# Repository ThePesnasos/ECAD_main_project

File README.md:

# ECAD_main_project
# Печатная плата для аналогового и цифровго трактов ЭЭГ
Для сборки аппарата ЭЭГ необходимо произвести 8 плат аналоговго тракта и 1 плату цифрового.
Плата цифрового тракта объединяется с 8 платами аналогового тракта

# TODO
1. В результате разводки платы выявлено отсутвие пинов для подключения питания 5В и 3,3 В.
Необходимо доработать схемотехническую часть, использовать разъёмы с большим числом пинов.

2. Предусмотреть отверстия под крепления печатных плат в корпусе устройства.

3. Рассмотреть возможность создания третьей "материнской", чтобы избежать использования разъемов с проводами внутри прибора.

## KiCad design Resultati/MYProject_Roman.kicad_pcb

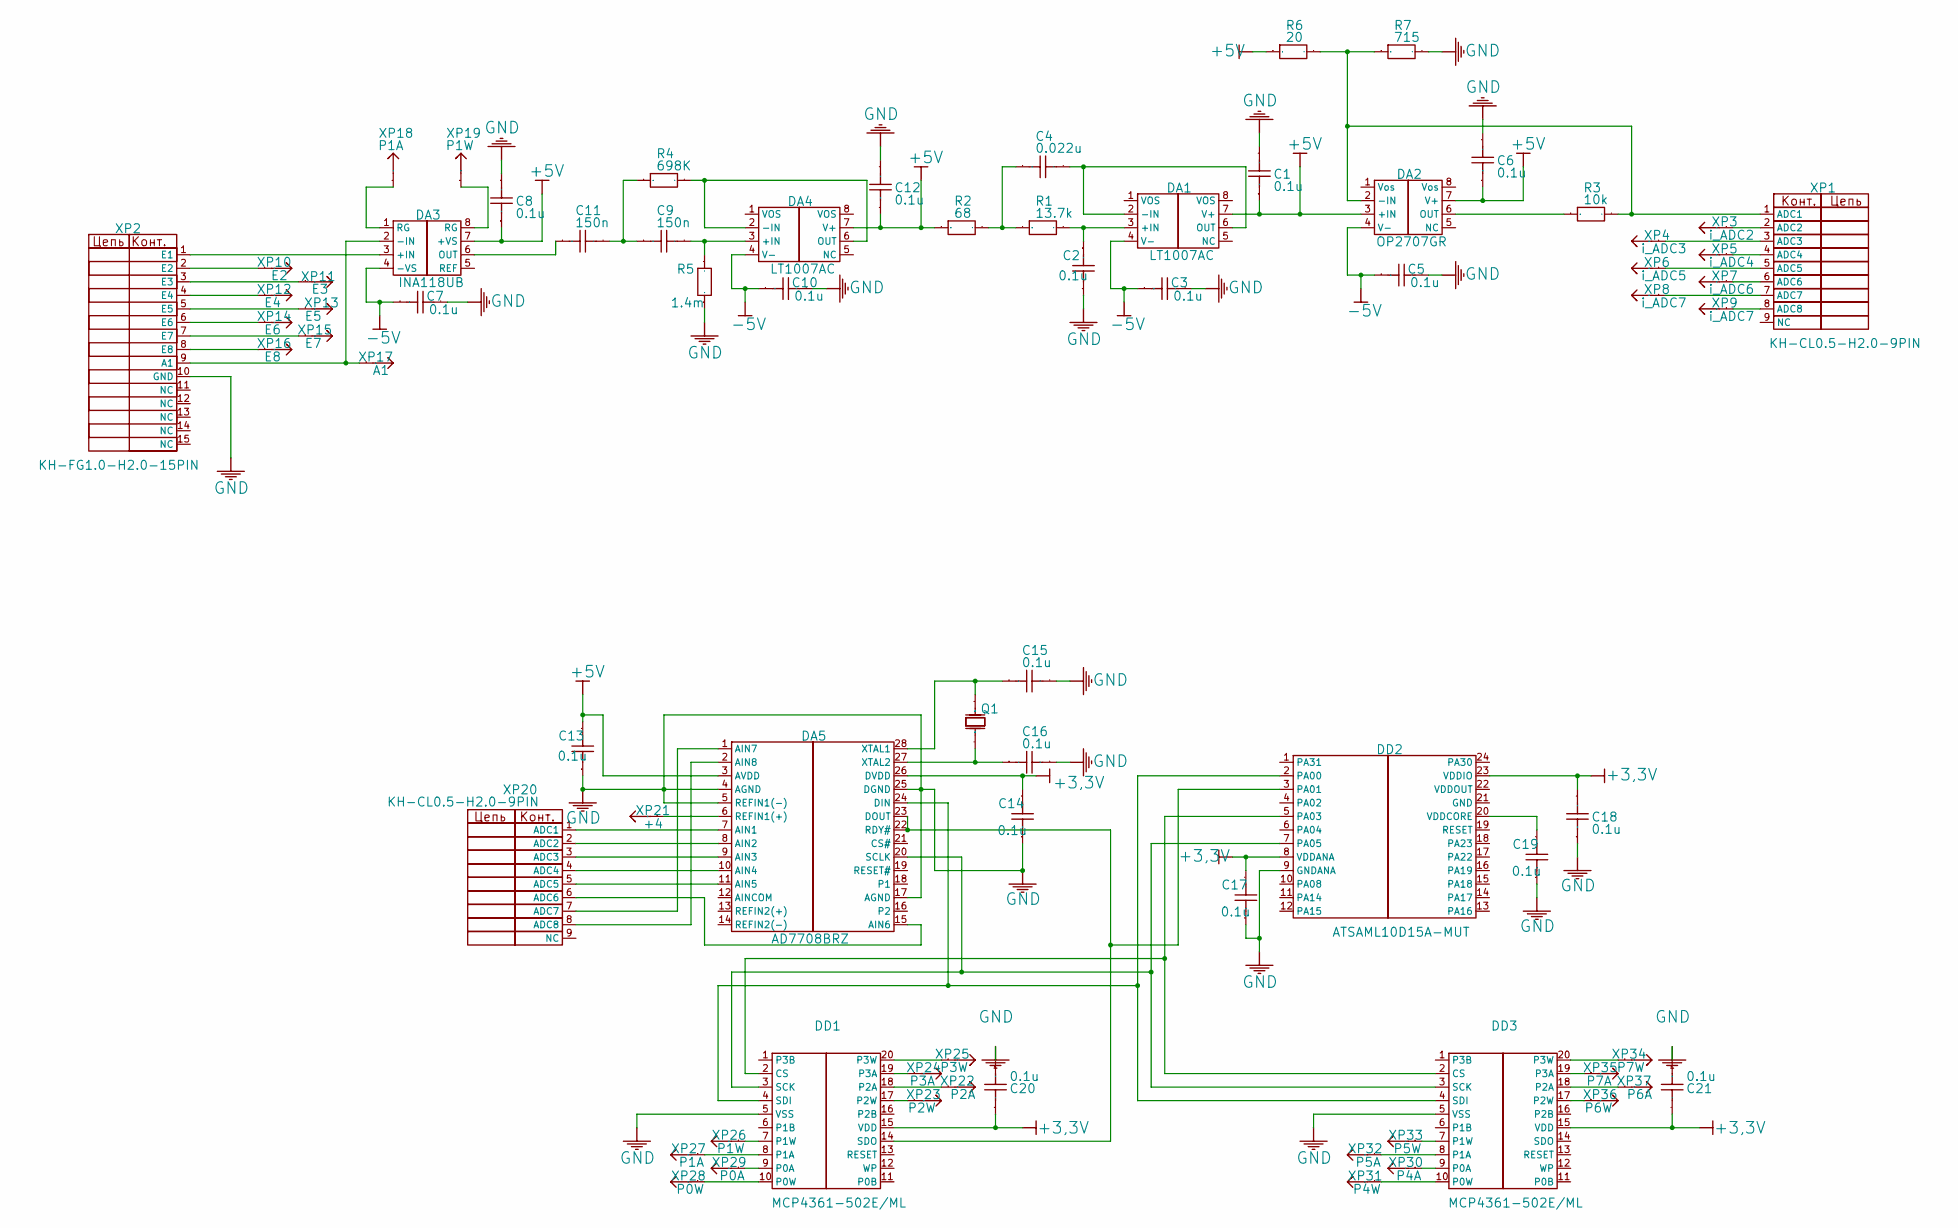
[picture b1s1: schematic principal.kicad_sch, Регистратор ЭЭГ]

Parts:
C1, C2, C3, C5, C6, C7, C8, C10, C12, C13, C14, C15, C16, C17, C18, C19, C20, C21: 0.1u
C4: 0.022u
C9, C11: 150n
DA1, DA4: LT1007AC; Manufacturer Part LT1007ACN8#PBF
DA2: OP2707GR; Manufacturer Part NJMOP277GR-TE1
DA3: INA118UB; Manufacturer Part INA118UB
DA5: AD7708BRZ; Manufacturer Part AD7708BRZ
DD1, DD3: MCP4361-502E/ML; Manufacturer Part MCP4361-502E/ML
DD2: ATSAML10D15A-MUT; Manufacturer Part ATSAML10D15A-MUT
Q1: HC-49SMD-XTAL_MD; Manufacturer Part HC-49SMD-XTAL_MD
R1: 13.7k
R2: 68
R3: 10k
R4: 698K
R5: 1.4m
R6: 20
R7: 715
XP1, XP20: KH-CL0.5-H2.0-9PIN; Manufacturer Part KH-CL0.5-H2.0-9PIN
XP2: KH-FG1.0-H2.0-15PIN; Manufacturer Part KH-FG1.0-H2.0-15PIN
XP3: i_ADC2
XP4: i_ADC3
XP5: i_ADC4
XP6: i_ADC5
XP7: i_ADC6
XP8, XP9: i_ADC7
XP10: E2
XP11: E3
XP12: E4
XP13: E5
XP14: E6
XP15: E7
XP16: E8
XP17: A1
XP18, XP27: P1A
XP19, XP26: P1W
XP21: +4
XP22: P2A
XP23: P2W
XP24: P3A
XP25: P3W
XP28: P0W
XP29: P0A
XP30: P4A
XP31: P4W
XP32: P5A
XP33: P5W
XP34: P7W
XP35: P7A
XP36: P6W
XP37: P6A

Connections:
+3,3V: C14.2, C17.2, C18.2, C20.2, C21.2, DA5.26 (DVDD), DD1.15 (VDD), DD2.8 (VDDANA), DD2.23 (VDDIO), DD3.15 (VDD)
-5V: C3.1, C5.1, C7.1, C10.1, DA1.4 (V-), DA2.4 (V−), DA3.4 (-VS), DA4.4 (V-)
DA1_1: DA1.1 (VOS)
DA1_2: C4.2, DA1.2 (-IN), DA1.6 (OUT)
DA1_3: C2.1, DA1.3 (+IN), R1.2
DA1_5: DA1.5 (NC)
DA1_8: DA1.8 (VOS)
DA2_1: DA2.1 (Vos)
DA2_2: DA2.2 (−IN), R3.2, R6.2, R7.1, XP1.1 (ADC1)
DA2_5: DA2.5 (NC)
DA2_6: DA2.6 (OUT), R3.1
DA2_8: DA2.8 (Vos)
DA3_1: DA3.1 (RG), XP18.1
DA3_5: DA3.5 (REF)
DA3_8: DA3.8 (RG), XP19.1
DA4_1: DA4.1 (VOS)
DA4_2: DA4.2 (-IN), DA4.6 (OUT), R4.2
DA4_3: C9.2, DA4.3 (+IN), R5.2
DA4_5: DA4.5 (NC)
DA4_8: DA4.8 (VOS)
DA5_6: DA5.6 (REFIN1(+)), XP21.1
DA5_12: DA5.12 (AINCOM)
DA5_13: DA5.13 (REFIN2(+))
DA5_14: DA5.14 (REFIN2(-))
DA5_16: DA5.16 (P2)
DA5_18: DA5.18 (P1)
DA5_19: DA5.19 (RESET#)
DA5_20: DA5.20 (SCLK), DD1.3 (SCK), DD2.7 (PA05), DD3.3 (SCK)
DA5_21: DA5.21 (CS#)
DA5_24: DA5.24 (DIN), DD1.4 (SDI), DD2.2 (PA00), DD3.4 (SDI)
DA5_27: C16.1, DA5.27 (XTAL2), Q1.2 (OSC2)
DA5_28: C15.1, DA5.28 (XTAL1), Q1.1 (OSC1)
DD1_1: DD1.1 (P3B)
DD1_6: DD1.6 (P1B)
DD1_7: DD1.7 (P1W), XP26.1
DD1_8: DD1.8 (P1A), XP27.1
DD1_9: DD1.9 (P0A), XP29.1
DD1_10: DD1.10 (P0W), XP28.1
DD1_11: DD1.11 (P0B)
DD1_12: DD1.12 (WP)
DD1_13: DD1.13 (RESET)
DD1_16: DD1.16 (P2B)
DD1_17: DD1.17 (P2W), XP23.1
DD1_18: DD1.18 (P2A), XP22.1
DD1_19: DD1.19 (P3A), XP24.1
DD1_20: DD1.20 (P3W), XP25.1
DD2_1: DD2.1 (PA31)
DD2_4: DD2.4 (PA02)
DD2_5: DD1.2 (CS), DD2.5 (PA03), DD3.2 (CS)
DD2_6: DD2.6 (PA04)
DD2_10: DD2.10 (PA08)
DD2_11: DD2.11 (PA14)
DD2_12: DD2.12 (PA15)
DD2_13: DD2.13 (PA16)
DD2_14: DD2.14 (PA17)
DD2_15: DD2.15 (PA18)
DD2_16: DD2.16 (PA19)
DD2_17: DD2.17 (PA22)
DD2_18: DD2.18 (PA23)
DD2_19: DD2.19 (RESET)
DD2_20: C19.2, DD2.20 (VDDCORE)
DD2_21: DD2.21 (GND)
DD2_22: DD2.22 (VDDOUT)
DD2_24: DD2.24 (PA30)
DD3_1: DD3.1 (P3B)
DD3_6: DD3.6 (P1B)
DD3_7: DD3.7 (P1W), XP33.1
DD3_8: DD3.8 (P1A), XP32.1
DD3_9: DD3.9 (P0A), XP30.1
DD3_10: DD3.10 (P0W), XP31.1
DD3_11: DD3.11 (P0B)
DD3_12: DD3.12 (WP)
DD3_13: DD3.13 (RESET)
DD3_14: DD3.14 (SDO)
DD3_16: DD3.16 (P2B)
DD3_17: DD3.17 (P2W), XP36.1
DD3_18: DD3.18 (P2A), XP37.1
DD3_19: DD3.19 (P3A), XP35.1
DD3_20: DD3.20 (P3W), XP34.1
GND: C1.2, C2.2, C3.2, C5.2, C6.2, C7.2, C8.2, C10.2, C12.2, C13.1, C14.1, C15.2, C16.2, C17.1, C18.1, C19.1, C20.1, C21.1, DA5.4 (AGND), DA5.5 (REFIN1(-)), DA5.17 (AGND), DA5.25 (DGND), DD1.5 (VSS), DD2.9 (GNDANA), DD3.5 (VSS), R5.1, R7.2, XP2.10 (GND)
R1_1: C4.1, R1.1, R2.2
R4_1: C9.1, C11.2, R4.1
XP1_2: XP1.2 (ADC2), XP3.1
XP1_3: XP1.3 (ADC3), XP4.1
XP1_4: XP1.4 (ADC4), XP5.1
XP1_5: XP1.5 (ADC5), XP6.1
XP1_6: XP1.6 (ADC6), XP7.1
XP1_7: XP1.7 (ADC7), XP8.1
XP1_8: XP1.8 (ADC8), XP9.1
XP1_9: XP1.9 (NC)
XP2_1: DA3.3 (+IN), XP2.1 (E1)
XP2_2: XP2.2 (E2), XP10.1
XP2_3: XP2.3 (E3), XP11.1
XP2_4: XP2.4 (E4), XP12.1
XP2_5: XP2.5 (E5), XP13.1
XP2_6: XP2.6 (E6), XP14.1
XP2_7: XP2.7 (E7), XP15.1
XP2_8: XP2.8 (E8), XP16.1
XP2_9: DA3.2 (-IN), XP2.9 (A1), XP17.1
XP2_11: XP2.11 (NC)
XP2_12: XP2.12 (NC)
XP2_13: XP2.13 (NC)
XP2_14: XP2.14 (NC)
XP2_15: XP2.15 (NC)
XP20_1: DA5.7 (AIN1), XP20.1 (ADC1)
XP20_2: DA5.8 (AIN2), XP20.2 (ADC2)
XP20_3: DA5.9 (AIN3), XP20.3 (ADC3)
XP20_4: DA5.10 (AIN4), XP20.4 (ADC4)
XP20_5: DA5.11 (AIN5), XP20.5 (ADC5)
XP20_6: DA5.15 (AIN6), XP20.6 (ADC6)
XP20_7: DA5.1 (AIN7), XP20.7 (ADC7)
XP20_8: DA5.2 (AIN8), XP20.8 (ADC8)
XP20_9: XP20.9 (NC)

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
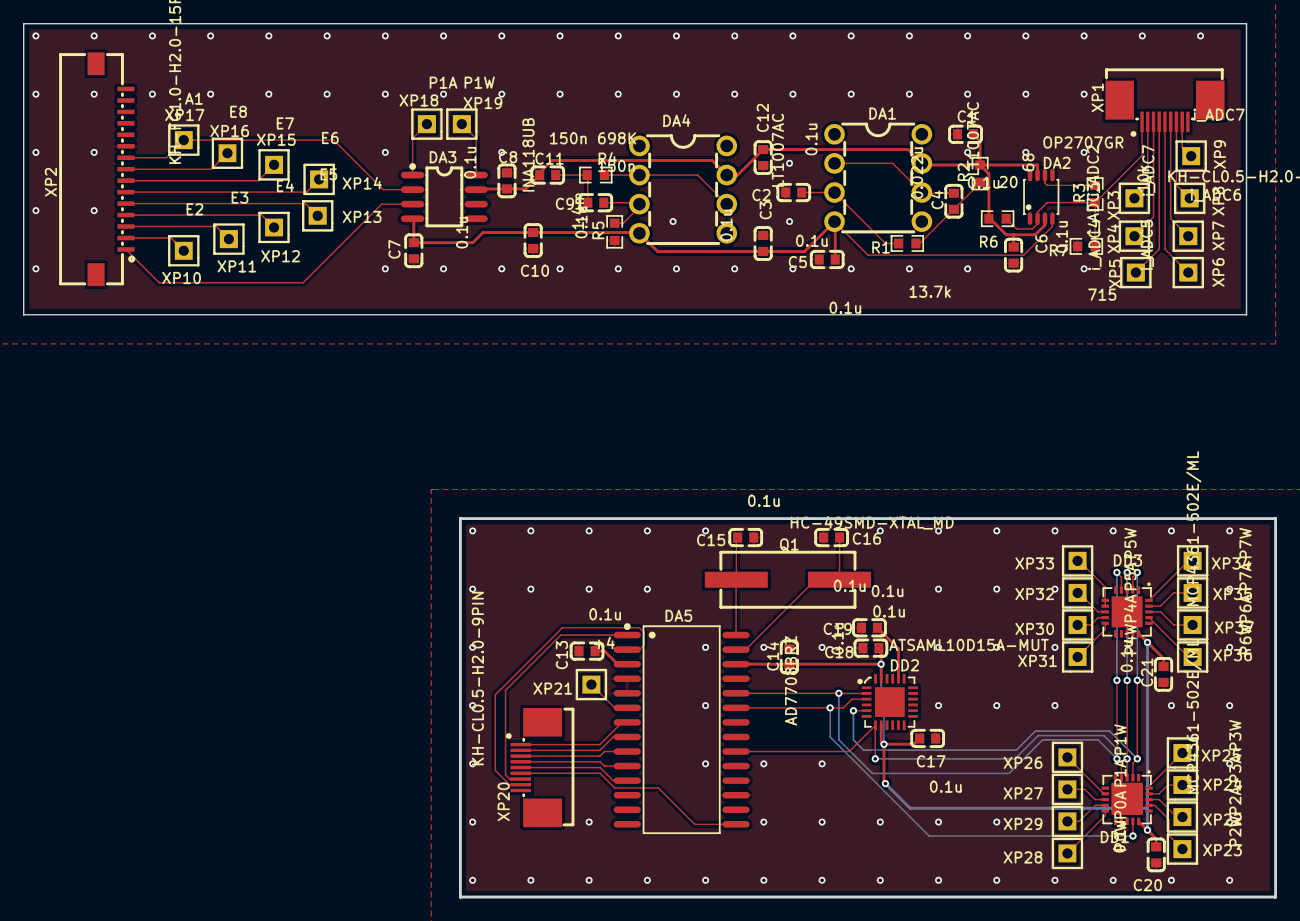
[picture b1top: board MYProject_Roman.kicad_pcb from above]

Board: 2 copper layers, 109.2 x 76.1 mm, 75 parts (0 on the bottom side), 62 nets.

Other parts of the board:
Pad_gge10147: Pad_gge10147

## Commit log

2025-10-31 Добавлена папка с результатами работы. Добавлена электрическая схема обоих плат
2025-10-31 Добавлена разводка
2025-10-31 Добавлены гербер файлы и файлы сверления
2025-10-31 Добавлены 3D модели
2025-10-31 Добавлена копия проекта
2025-10-31 Обновлён README файл
